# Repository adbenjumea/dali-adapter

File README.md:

# DALI adapter for Arduino Nano
This project was made for the subject "Automatización de Edificios Inteligentes" in the Industrial Engineering Master Degree (University of Seville)

Author:
- Diego J. Benjumea

This is a physical implementation of the DALI protocol for a home automation installation, and some of its commands using Arduino Nano boards and simple electronics.

## Physical implementation
The bus has been build as follow

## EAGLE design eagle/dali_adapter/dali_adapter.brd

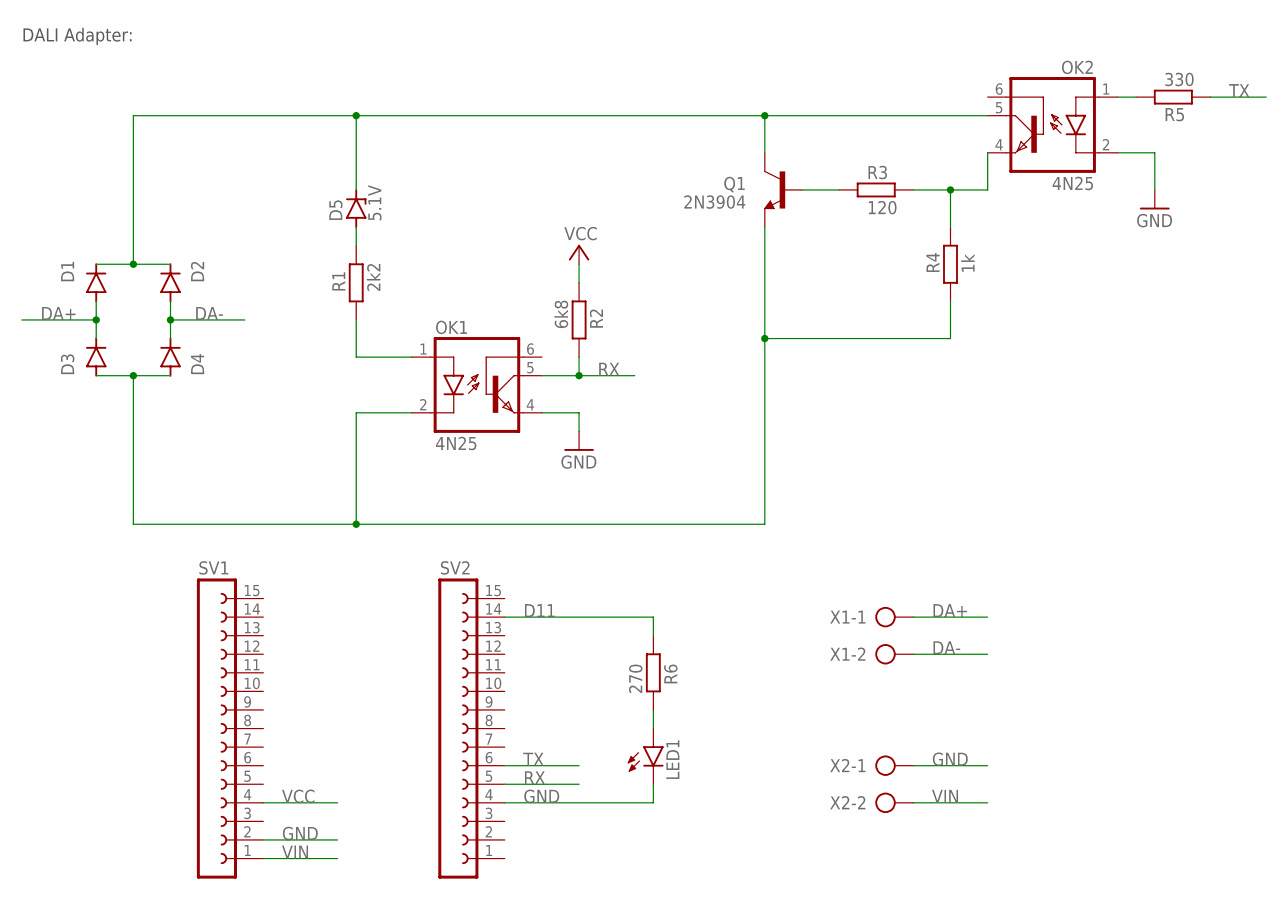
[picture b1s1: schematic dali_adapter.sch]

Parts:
D1, D2, D3, D4: 1N4004; DO41-10
D5: 5.1V; DO35Z10
LED1: LED5MM
OK1, OK2: 4N25; DIL06
Q1: 2N3904; TO92-EBC
R1: 2k2; 0207/10
R2: 6k8; 0207/10
R3: 120; 0207/10
R4: 1k; 0207/10
R5: 330; 0207/10
R6: 270; 0207/10
SV1, SV2: FE15-1; FE15
X1, X2: AK500/2

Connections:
D11: R6.1, SV2.14
DA+: D1.A, D3.C, X1.1
DA-: D2.A, D4.C, X1.2
GND: LED1.K (C), OK1.4 (EMI), OK2.2 (C), SV1.2, SV2.4, X2.1
unnamed: LED1.A, R6.2
unnamed: D3.A, D4.A, OK1.2 (C), Q1.E, R4.1
unnamed: OK1.1 (A), R1.1
unnamed: OK2.4 (EMI), R3.2, R4.2
unnamed: Q1.B, R3.1
unnamed: OK2.1 (A), R5.2
unnamed: D5.A, R1.2
unnamed: D1.C, D2.C, D5.C, OK2.5 (COL), Q1.C
RX: OK1.5 (COL), R2.2, SV2.5
TX: R5.1, SV2.6
VCC: R2.1, SV1.4
VIN: SV1.1, X2.2

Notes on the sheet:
DALI Adapter:

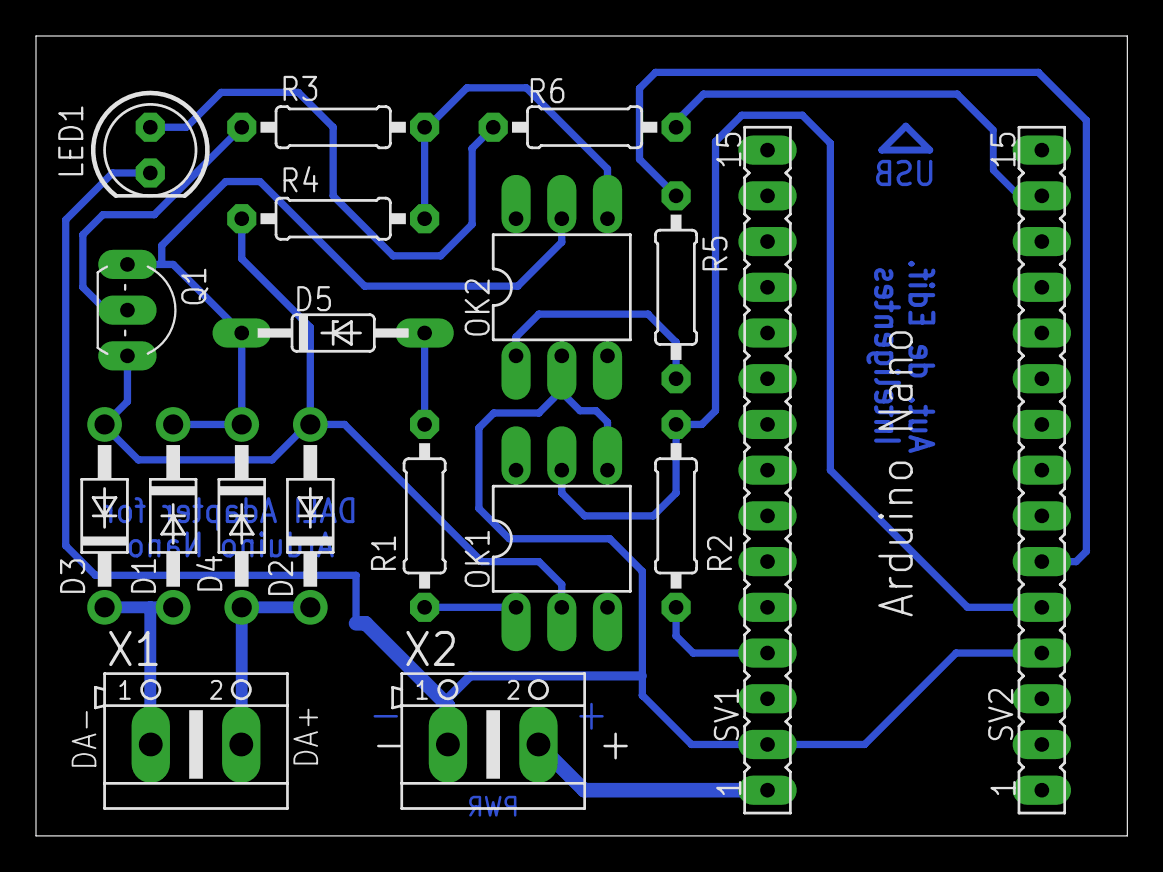
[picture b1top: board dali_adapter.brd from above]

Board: 2 copper layers, 60.6 x 44.4 mm, 19 parts (0 on the bottom side), 16 nets.

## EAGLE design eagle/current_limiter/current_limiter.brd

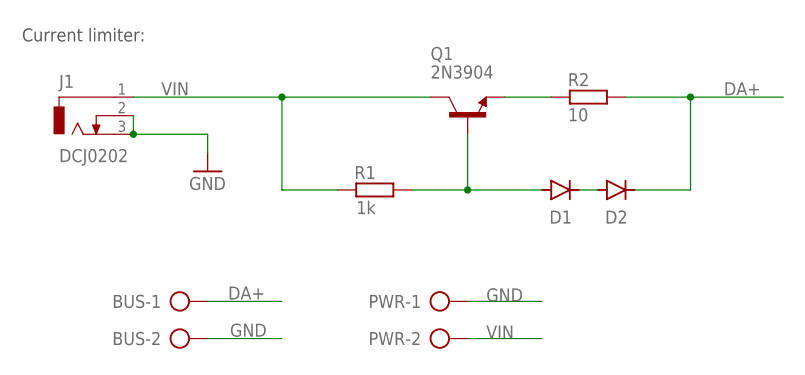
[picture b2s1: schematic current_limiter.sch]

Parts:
BUS: AK500/2
D1, D2: 1N4004; DO41-10
J1: DCJ0202
PWR: AK500/2
Q1: 2N3904; TO92-EBC
R1: 1k; 0207/10
R2: 10; 0207/10

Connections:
DA+: BUS.1, D2.C, R2.2
GND: BUS.2, J1.2, J1.3, PWR.1
unnamed: D1.A, Q1.B, R1.2
unnamed: D1.C, D2.A
unnamed: Q1.E, R2.1
VIN: J1.1, PWR.2, Q1.C, R1.1

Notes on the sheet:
Current limiter:

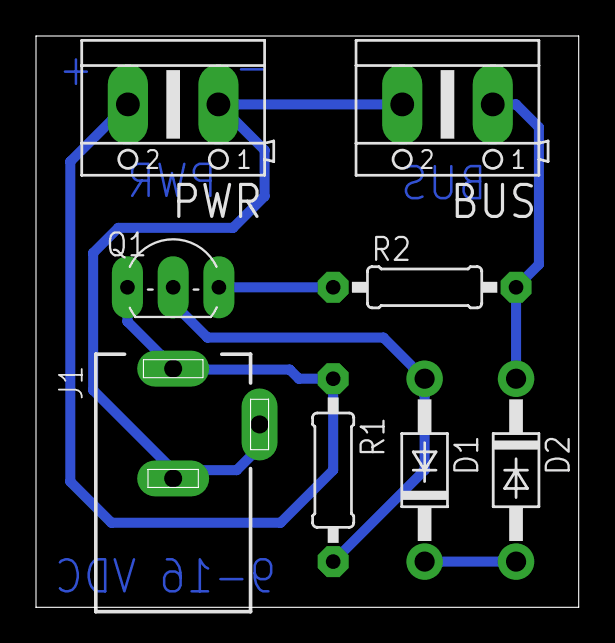
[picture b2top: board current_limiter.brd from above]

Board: 2 copper layers, 30.1 x 31.7 mm, 8 parts (0 on the bottom side), 6 nets.
